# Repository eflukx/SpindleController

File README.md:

# CNC Spindle Controller

Hardware and firmware for (PID) controlling universal AC motors (e.g. CNC spindles)

Device to precicely control the spindle speed of a CNC machine. I'm using a  Kress 530FM 530Watt spindle, but Anything upto 1000 Watt should probably be no problem. The design is based on https://sites.google.com/site/klaasdc/cnc-router/spindle-controller (thanks for finding a spot to mount the optical pickup Klaas!).

I've added a nice -mostly single sided- PCB and bases the design on the ubiquitous ATMega328p AVR platform. The PCB is designed to be easily built, using a mostly single sided design and through hole parts. Please be aware that the board carries lethal 230VAC mains supply. Proceed at your own risk! DisclaimerL: I take no liability whatsoever, you're on your own. Damage to spindle, fried PC, cats on fire, all your problem.!

The spindle speed is controlled by means of an optical pickup (rotational pulse) and a PID loop. A break-off mini-board with the TCRT5000 optical pickup to fit inside the Kress 530FM spindle is included in the PCB design.

## Power supply
The board includes a 6 volt mains transformer which supplies the logic power. The power supply may be omitted when the circuit is powered from the headers. Probably using the 5V out of a USB Serial (TTL!) cable will suffice to power the circuit. 

To minimize dissipation, I've chosen a 6V transformer in conjunction with a low drop linear (LDO) regulator. Alternatively you can use a standard 7805, but a slightly higher input voltage is needed. A 8-9 volt transformer will do, the heat dissipation from the 7805 will be a bit higher. Probably you'll still be ok with the ground plane as heatsink, otherwise place a small heatsink.

## Planned for 1st release
- PID controlled speed via RPM pulse.
- Manual speed control via knob (rotary encoder)
- Old school LED display
- Computer control via I2C
- Computer control via Async Serial (UART)
- Simple power control without RPM pulse (without optical pickup)

## Not in the package, for a next version maybe?
- Different display (128x64 graphic?)
- (over) Current monitoring
- Fuse 
- Coffee maker
- Dancing partygirl

This was created using KiCAD nightly (april 2017), possibly you cannot load the files in the stable version

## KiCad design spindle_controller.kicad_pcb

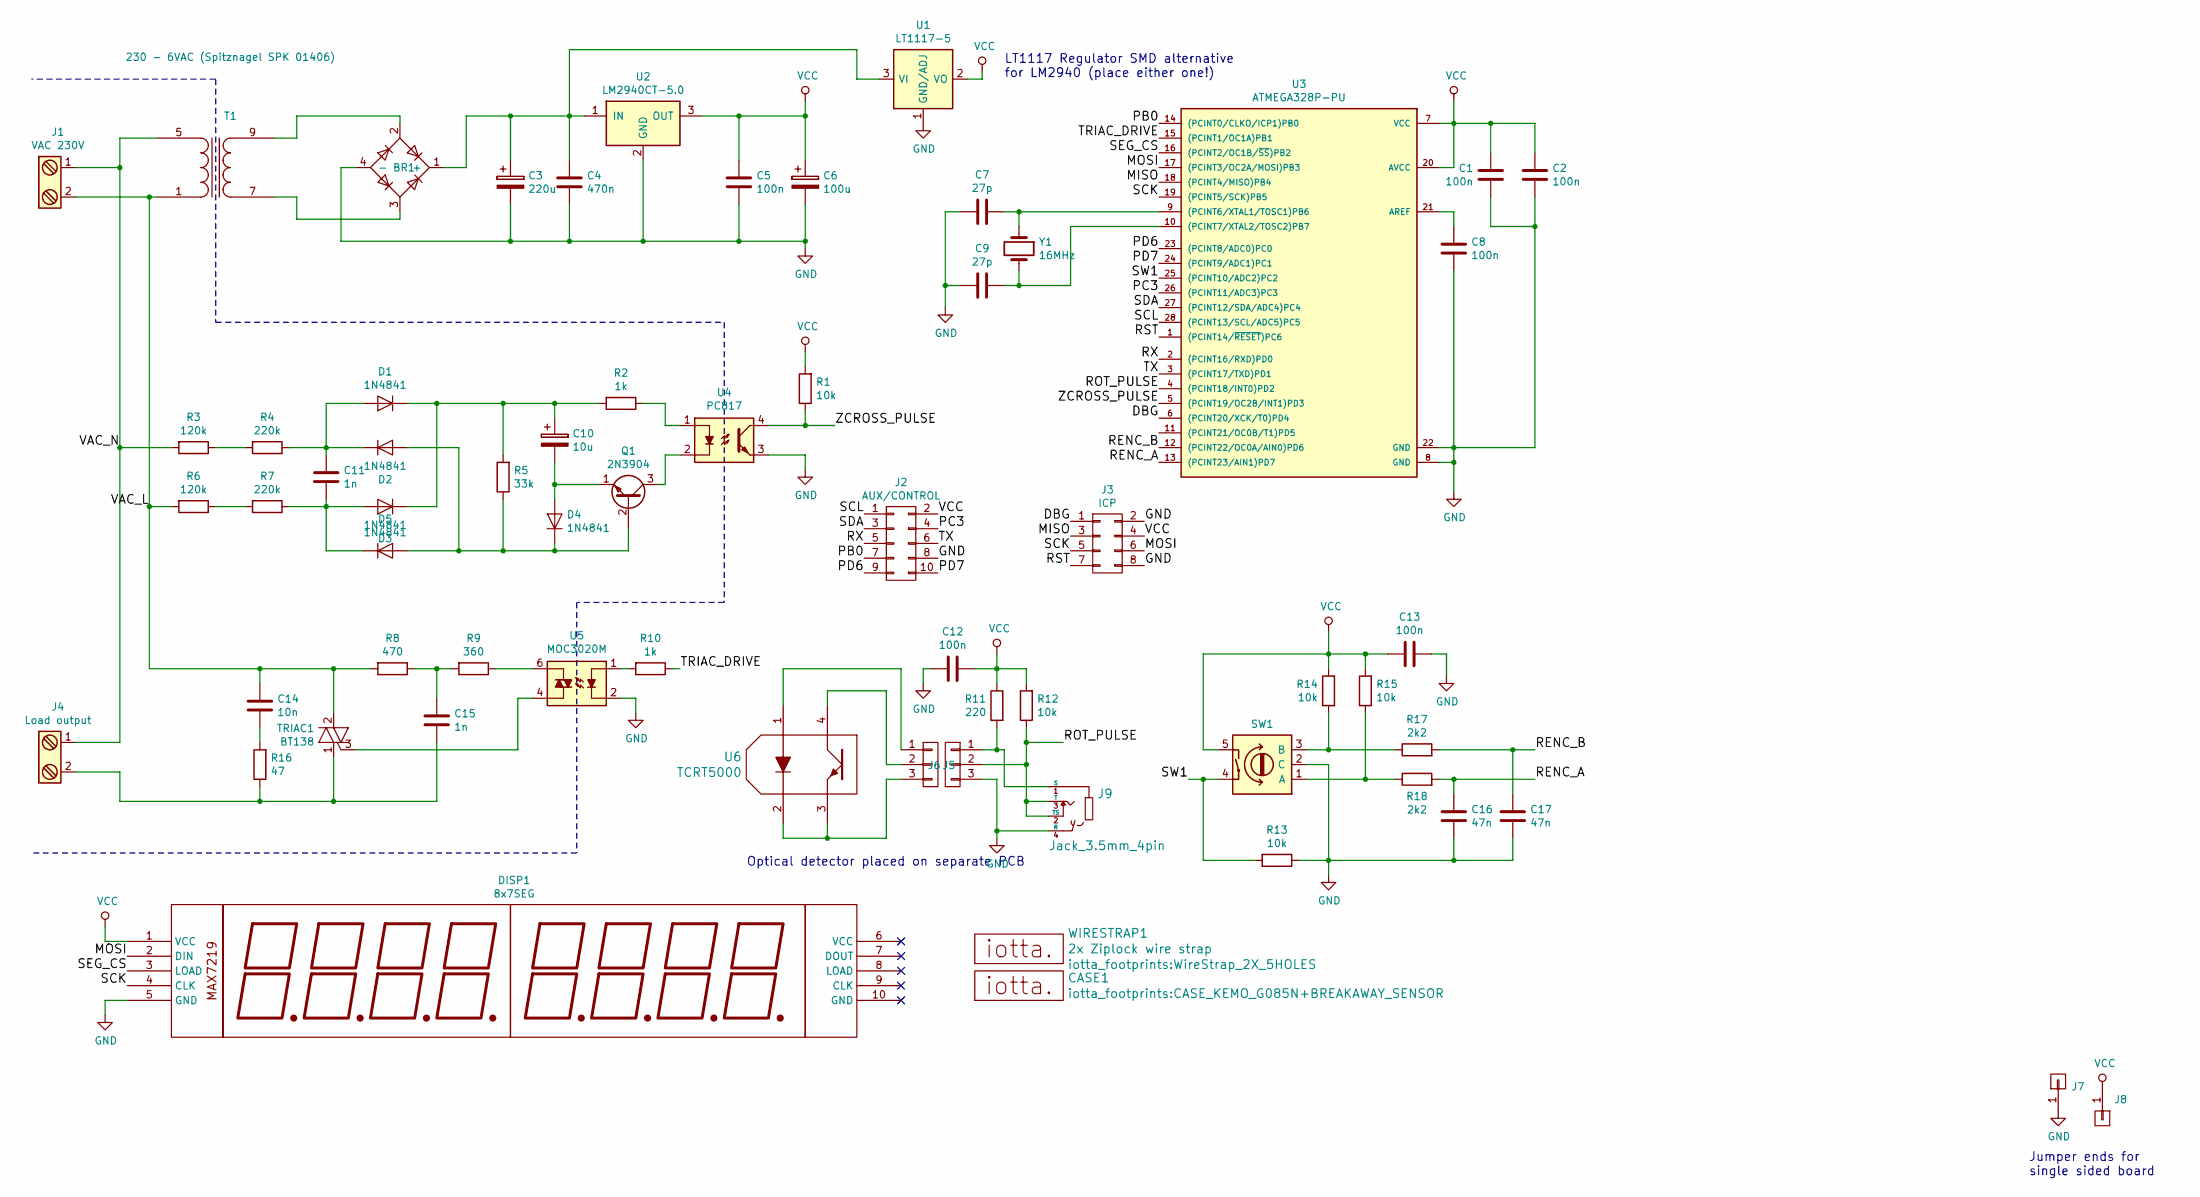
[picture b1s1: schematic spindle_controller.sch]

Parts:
BR1: D_Bridge_+AA-; bridge_wob
C1, C2, C5, C8, C12, C13: 100n; C_Rect_L7.0mm_W2.5mm_P5.00mm
C3: 220u; CP_Radial_D8.0mm_P3.50mm
C4: 470n; C_Rect_L7.0mm_W2.5mm_P5.00mm
C6: 100u; CP_Radial_D5.0mm_P2.00mm
C7, C9: 27p; C_Rect_L4.6mm_W2.0mm_P2.50mm_MKS02_FKP02
C10: 10u; CP_Radial_D5.0mm_P2.00mm
C11: 1n; C_Rect_L7.0mm_W2.5mm_P5.00mm
C14: 10n; C_Rect_L16.5mm_W5.0mm_P15.00mm_MKT
C15: 1n; C_Disc_D8.0mm_W5.0mm_P7.50mm
C16, C17: 47n; C_Rect_L7.0mm_W2.5mm_P5.00mm
CASE1: Case; CASE_KEMO_G085N+BREAKAWAY_SENSOR
D1, D2, D3, D4, D5: 1N4841; diode_do35
DISP1: 8x7SEG; Pin_Header_Straight_1x05_Pitch2.54mm
J1: VAC 230V; TerminalBlock_Pheonix_MKDS1.5-2pol
J2: AUX/CONTROL; Pin_Header_Angled_2x05_Pitch2.54mm
J3: ICP; Pin_Header_Angled_2x04_Pitch2.54mm
J4: Load output; TerminalBlock_Pheonix_MKDS1.5-2pol
J5, J6: CONN_01X03; Pin_Header_Angled_1x03_Pitch2.54mm
J7: GND_JUMPER; JUMPER_PIN
J8: VCC_JUMPER; JUMPER_PIN
J9: Jack_3.5mm_4pin; jack_3.5_sj1-3514-smt
Q1: 2N3904; TO-92_Molded_Narrow
R1, R12, R13, R14, R15: 10k; R_Axial_DIN0204_L3.6mm_D1.6mm_P7.62mm_Horizontal
R2, R10: 1k; R_Axial_DIN0204_L3.6mm_D1.6mm_P7.62mm_Horizontal
R3, R6: 120k; R_Axial_DIN0204_L3.6mm_D1.6mm_P7.62mm_Horizontal
R4, R7: 220k; R_Axial_DIN0204_L3.6mm_D1.6mm_P7.62mm_Horizontal
R5: 33k; R_Axial_DIN0204_L3.6mm_D1.6mm_P7.62mm_Horizontal
R8: 470; R_Axial_DIN0204_L3.6mm_D1.6mm_P7.62mm_Horizontal
R9: 360; R_Axial_DIN0204_L3.6mm_D1.6mm_P7.62mm_Horizontal
R11: 220; R_Axial_DIN0204_L3.6mm_D1.6mm_P7.62mm_Horizontal
R16: 47; R_Axial_DIN0414_L11.9mm_D4.5mm_P15.24mm_Horizontal
R17, R18: 2k2; R_Axial_DIN0204_L3.6mm_D1.6mm_P7.62mm_Horizontal
SW1: Rotary_Encoder_Switch; encoder_alps-ec12d
T1: 230 - 6VAC (Spitznagel SPK 01406); Trafo_CHK-EI30-2VA_1xSec
TRIAC1: BT138; TO-220_Vertical
U1: LT1117-5; SOT-223
U2: LM2940CT-5.0; TO-220_Horizontal_connected_tab
U3: ATMEGA328P-PU; DIP-28_W7.62mm
U4: PC817; DIP-4_W7.62mm
U5: MOC3020M; DIP-6_W7.62mm
U6: TCRT5000
WIRESTRAP1: 2x Ziplock wire strap; WireStrap_2X_5HOLES
Y1: 16MHz; Crystal_HC49-U_Vertical

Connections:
/DBG: J3.1, U3.6 ((PCINT20/XCK/T0)PD4)
/MISO: J3.3, U3.18 ((PCINT4/MISO)PB4)
/MOSI: DISP1.2 (DIN), J3.6, U3.17 ((PCINT3/OC2A/MOSI)PB3)
/PB0: J2.7, U3.14 ((PCINT0/CLKO/ICP1)PB0)
/PC3: J2.4, U3.26 ((PCINT11/ADC3)PC3)
/PD6: J2.9, U3.23 ((PCINT8/ADC0)PC0)
/PD7: J2.10, U3.24 ((PCINT9/ADC1)PC1)
/RENC_A: C16.2, R18.2, U3.13 ((PCINT23/AIN1)PD7)
/RENC_B: C17.2, R17.2, U3.12 ((PCINT22/OC0A/AIN0)PD6)
/ROT_PULSE: J6.2, J9.2 (TS), J9.3 (T), R12.1, U3.4 ((PCINT18/INT0)PD2)
/RST: J3.7, U3.1 ((PCINT14/~RESET~)PC6)
/RX: J2.5, U3.2 ((PCINT16/RXD)PD0)
/SCK: DISP1.4 (CLK), J3.5, U3.19 ((PCINT5/SCK)PB5)
/SCL: J2.1, U3.28 ((PCINT13/SCL/ADC5)PC5)
/SDA: J2.3, U3.27 ((PCINT12/SDA/ADC4)PC4)
/SEG_CS: DISP1.3 (LOAD), U3.16 ((PCINT2/OC1B/~SS~)PB2)
/SW1: R13.2, SW1.4, U3.25 ((PCINT10/ADC2)PC2)
/TRIAC_DRIVE: R10.1, U3.15 ((PCINT1/OC1A)PB1)
/TX: J2.6, U3.3 ((PCINT17/TXD)PD1)
/VAC_L: C14.1, J1.2, R6.2, R8.2, T1.1 (AA), TRIAC1.2 (A1)
/VAC_N: J1.1, J4.1, R3.2, T1.5 (AB)
/ZCROSS_PULSE: R1.1, U3.5 ((PCINT19/OC2B/INT1)PD3), U4.4
GND: BR1.4 (-), C1.2, C2.1, C3.2, C4.2, C5.2, C6.2, C7.2, C8.2, C9.2, C12.2, C13.1, C16.1, C17.1, DISP1.5 (GND), J2.8, J3.2, J3.8, J6.3, J7.1, J9.4 (R), R13.1, SW1.2 (C), U1.1 (GND/ADJ), U2.2 (GND), U3.8 (GND), U3.22 (GND), U4.3, U5.2; also elsewhere on the board
unnamed: BR1.1 (+), C3.1, C4.1, U1.3 (VI), U2.1 (IN)
unnamed: BR1.2, T1.9 (SA)
unnamed: BR1.3, T1.7 (SB)
unnamed: C7.1, U3.9 ((PCINT6/XTAL1/TOSC1)PB6), Y1.1
unnamed: C8.1, U3.21 (AREF)
unnamed: C9.1, U3.10 ((PCINT7/XTAL2/TOSC2)PB7), Y1.2
unnamed: C10.1, D1.1 (K), D3.1 (K), R2.2, R5.2
unnamed: C10.2, D4.2 (A), Q1.1 (E)
unnamed: C11.1, D1.2 (A), D2.1 (K), R4.1
unnamed: C11.2, D3.2 (A), D5.1 (K), R7.1
unnamed: C14.2, R16.2
unnamed: C15.1, R8.1, R9.2
unnamed: C15.2, J4.2, R16.1, TRIAC1.1 (A2)
unnamed: D2.2 (A), D4.1 (K), D5.2 (A), Q1.2 (B), R5.1
unnamed: J5.1, U6.1
unnamed: J5.2, U6.4
unnamed: J5.3, U6.2, U6.3
unnamed: J6.1, J9.1 (S), R11.2
unnamed: Q1.3 (C), U4.2
unnamed: R2.1, U4.1
unnamed: R3.1, R4.2
unnamed: R6.1, R7.2
unnamed: R9.1, U5.6
unnamed: R10.2, U5.1
unnamed: R14.1, R17.1, SW1.3 (B)
unnamed: R15.1, R18.1, SW1.1 (A)
unnamed: TRIAC1.3 (G), U5.4
VCC: C1.1, C2.2, C5.1, C6.1, C12.1, C13.2, DISP1.1 (VCC), J2.2, J3.4, J8.1, R1.2, R11.1, R12.2, R14.2, R15.2, SW1.5, U1.2 (VO), U1.4 (VO), U2.3 (OUT), U3.7 (VCC), U3.20 (AVCC); also elsewhere on the board

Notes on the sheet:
Optical detector placed on separate PCB
LT1117 Regulator SMD alternative for LM2940 (place either one!)
Jumper ends for single sided board

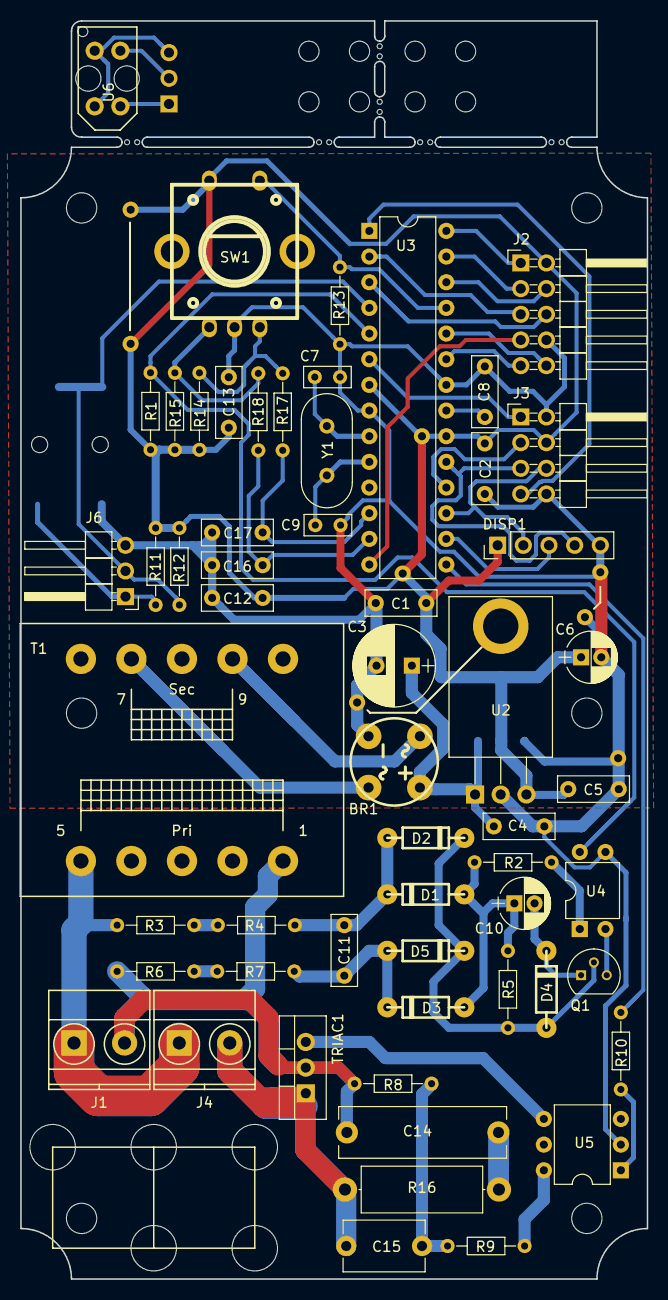
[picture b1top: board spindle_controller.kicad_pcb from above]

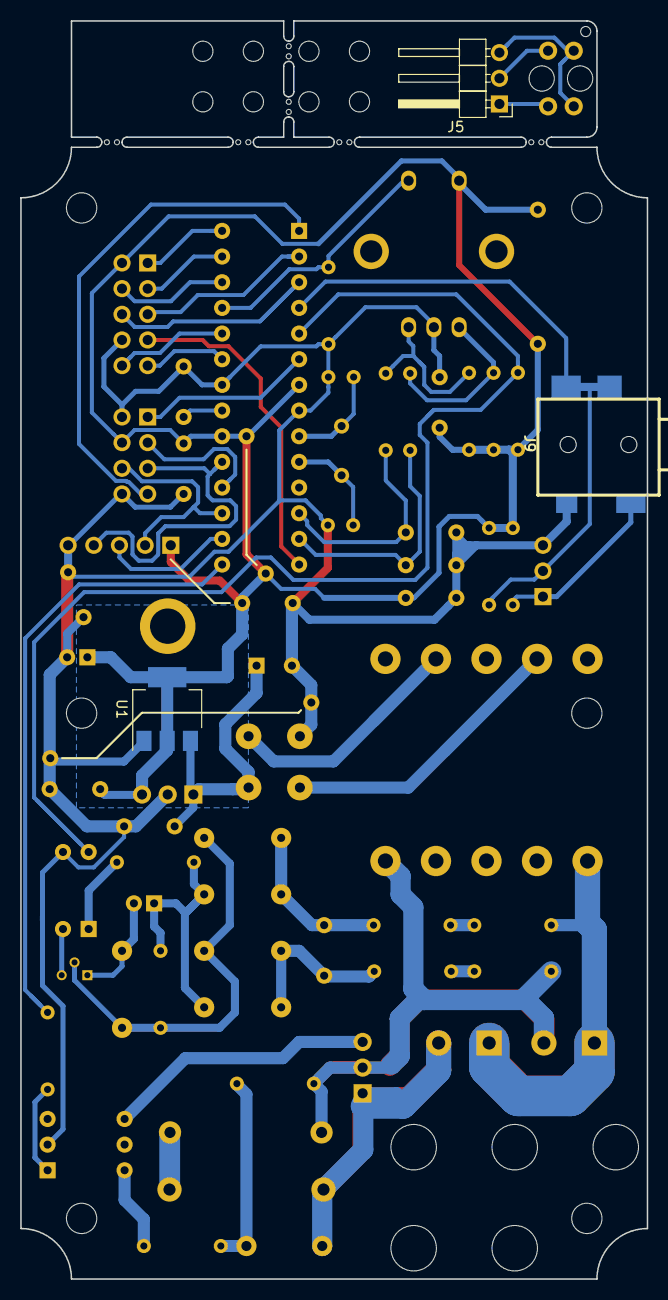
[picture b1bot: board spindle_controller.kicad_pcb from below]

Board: 2 copper layers, 62.0 x 124.5 mm, 70 parts (3 on the bottom side), 51 nets.

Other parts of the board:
J7#2, J7#3, J7#4: GND_JUMPER; JUMPER_PIN
J8#2, J8#3, J8#4: VCC_JUMPER; JUMPER_PIN

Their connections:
GND: J7#2.1, J7#3.1, J7#4.1; also elsewhere on the board
VCC: J8#2.1, J8#3.1, J8#4.1; also elsewhere on the board

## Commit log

2017-04-14 Add schematic and footprints
2017-04-14 Add board routing halfway
2017-04-15 Add shuffled AC cord entry, ziplock holes, 1117 regulator alternative, shuffled linear supply
2017-04-15 Finish routing. Need to draw break-off slots.
2017-04-16 Add jumper wires for single sided PCB's
2017-04-16 Add breakaway board for optical sensor, general board updates, dissipation planes, screw clearances and silkscreen
2017-04-17 Trying to __squeeze__ in a heatsink for the TRIAC, routing suffers.
2017-05-18 Rearranged pin ouputs (PB0 and PC3 now separate), added rotary debounce (not on PCB yet), added 3mm jack for optical pickup
2017-05-20 Add some "firmware", currently only drives the display
2017-05-20 Add debounce RC network on rotary encoder, improved single sided routing. Higher clearances where possible better result when milling (routing :)) the board.
2017-05-30 Small updates to VCC plane at 1117 regulator.
2017-06-07 Place value fields on PCB
2017-06-07 Add reset button
2017-06-12 Add drivers, console, libraries and much of the basic stuff we need.
2017-06-12 Add zero_cross (test), simple (m)sec timer and then some
2017-06-14 Update 7 Segment driver, uses bitmap font, SPI and made some extensions
2017-06-14 Add first cuts of opto, triac and zero-cross drivers and some supporting drivers/libs
2017-06-16 Fix rotary switch, Add accelerated mode. Things got a lot simpler also :)
2017-06-16 Fix merge
